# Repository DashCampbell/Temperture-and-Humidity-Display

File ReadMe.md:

# Temperature & Humidity Display

A basic PCB displaying the temperature and humidity from a sensor to a OLED screen.

* Uses a STM32 microcontroller with SWD.
* Uses FreeRTOS to run tasks concurrently.
* Uses I2C to communicate with the OLED display and sensor.
* Uses PWM to controll a RGB addressable LED.

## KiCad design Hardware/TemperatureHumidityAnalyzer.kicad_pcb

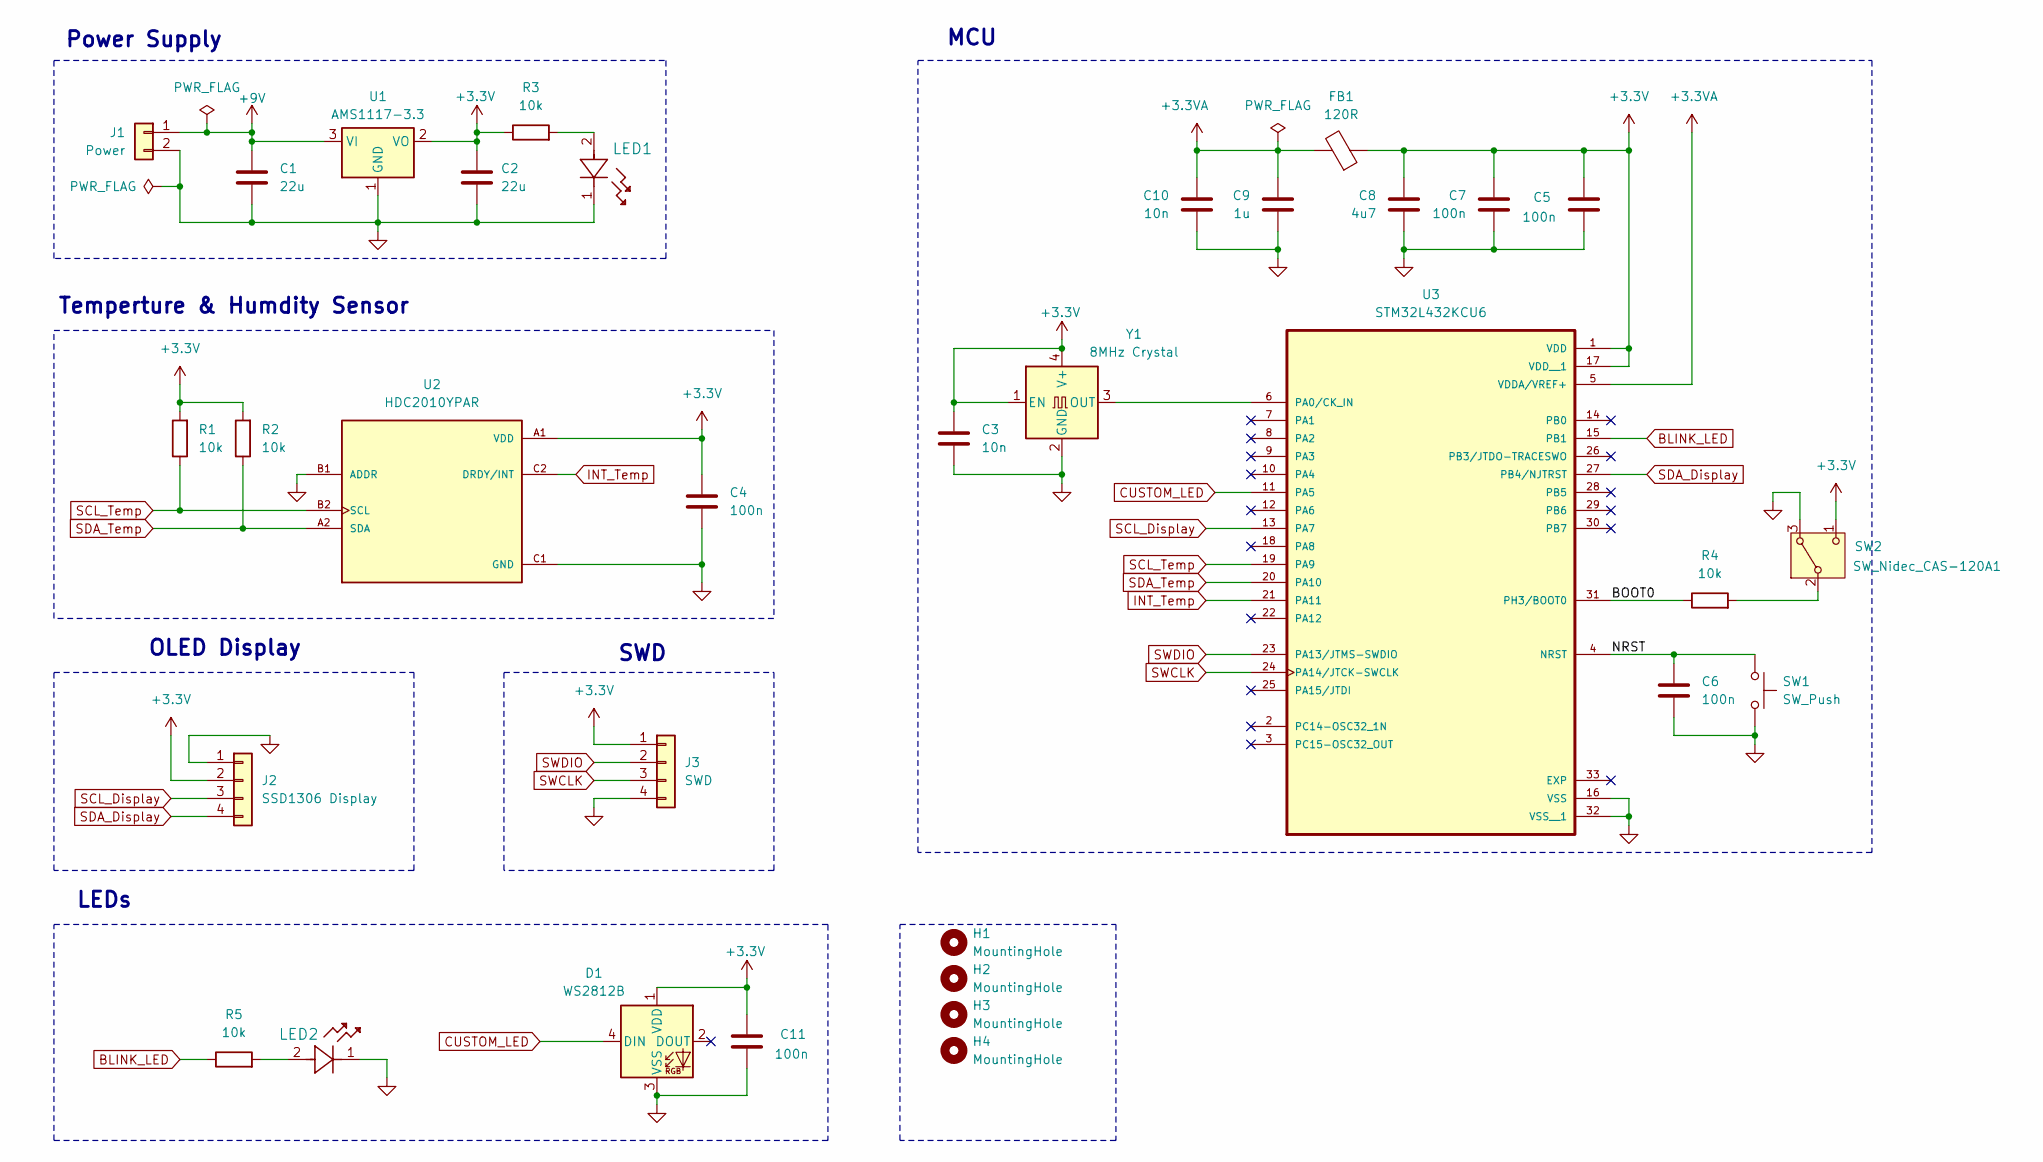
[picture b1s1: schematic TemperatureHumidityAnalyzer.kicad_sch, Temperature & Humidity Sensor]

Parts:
C1, C2: 22u; C_0805_2012Metric_Pad1.18x1.45mm_HandSolder
C3, C10: 10n; C_0603_1608Metric_Pad1.08x0.95mm_HandSolder
C4, C5, C6, C7, C11: 100n; C_0603_1608Metric_Pad1.08x0.95mm_HandSolder
C8: 4u7; C_0603_1608Metric_Pad1.08x0.95mm_HandSolder
C9: 1u; C_0603_1608Metric_Pad1.08x0.95mm_HandSolder
D1: WS2812B; LED_OPSCO_SK6812_PLCC4_5.0x5.0mm_P3.1mm
FB1: 120R; L_0603_1608Metric_Pad1.05x0.95mm_HandSolder
H1, H2, H3, H4: MountingHole; MountingHole_2.2mm_M2
J1: Power; PinSocket_1x02_P2.54mm_Vertical
J2: SSD1306 Display; SSD1306
J3: SWD; PinHeader_1x04_P2.54mm_Vertical
LED1, LED2: LTST-C170KGKT; LED_LTST-C170KGKT_LTO
R1, R2, R4, R5: 10k; R_0603_1608Metric_Pad0.98x0.95mm_HandSolder
R3: 10k; R_0805_2012Metric_Pad1.20x1.40mm_HandSolder
SW1: SW_Push; SW_PUSH_6mm
SW2: SW_Nidec_CAS-120A1; Nidec_Copal_CAS-120A
U1: AMS1117-3.3; SOT-223-3_TabPin2
U2: HDC2010YPAR; BGA6C100X50P2X3_HDC2010YPAR; PARTREV C
U3: STM32L432KCU6; PARTREV 3
Y1: 8MHz Crystal; Oscillator_SMD_EuroQuartz_XO32-4Pin_3.2x2.5mm

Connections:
+3.3V: C2.1, C3.1, C4.1, C5.1, C7.1, C8.1, C11.1, D1.1 (VDD), FB1.1, J2.2, J3.1, R1.2, R2.2, R3.1, SW2.1 (C), U1.2 (VO), U2.A1 (VDD), U3.1 (VDD), U3.17 (VDD__1), Y1.1 (EN), Y1.4 (V+)
+3.3VA: C9.1, C10.1, FB1.2, U3.5 (VDDA/VREF+)
+9V: C1.1, J1.1, U1.3 (VI)
/BOOT0: R4.1, U3.31 (PH3/BOOT0)
/NRST: C6.1, SW1.1, U3.4 (NRST)
BLINK_LED: R5.1, U3.15 (PB1)
CUSTOM_LED: D1.4 (DIN), U3.11 (PA5)
GND: C1.2, C2.2, C3.2, C4.2, C5.2, C6.2, C7.2, C8.2, C9.2, C10.2, C11.2, D1.3 (VSS), J1.2, J2.1, J3.4, LED1.1, LED2.1, SW1.2, SW2.3 (A), U1.1 (GND), U2.B1 (ADDR), U2.C1 (GND), U3.16 (VSS), U3.32 (VSS__1), Y1.2 (GND)
INT_Temp: U2.C2 (DRDY/INT), U3.21 (PA11)
unnamed: LED1.2, R3.2
unnamed: LED2.2, R5.2
unnamed: R4.2, SW2.2 (B)
unnamed: U3.6 (PA0/CK_IN), Y1.3 (OUT)
SCL_Display: J2.3, U3.13 (PA7)
SCL_Temp: R1.1, U2.B2 (SCL), U3.19 (PA9)
SDA_Display: J2.4, U3.27 (PB4/NJTRST)
SDA_Temp: R2.1, U2.A2 (SDA), U3.20 (PA10)
SWCLK: J3.3, U3.24 (PA14/JTCK-SWCLK)
SWDIO: J3.2, U3.23 (PA13/JTMS-SWDIO)

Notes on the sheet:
OLED Display
Power Supply
SWD
Temperture & Humdity Sensor
LEDs
MCU

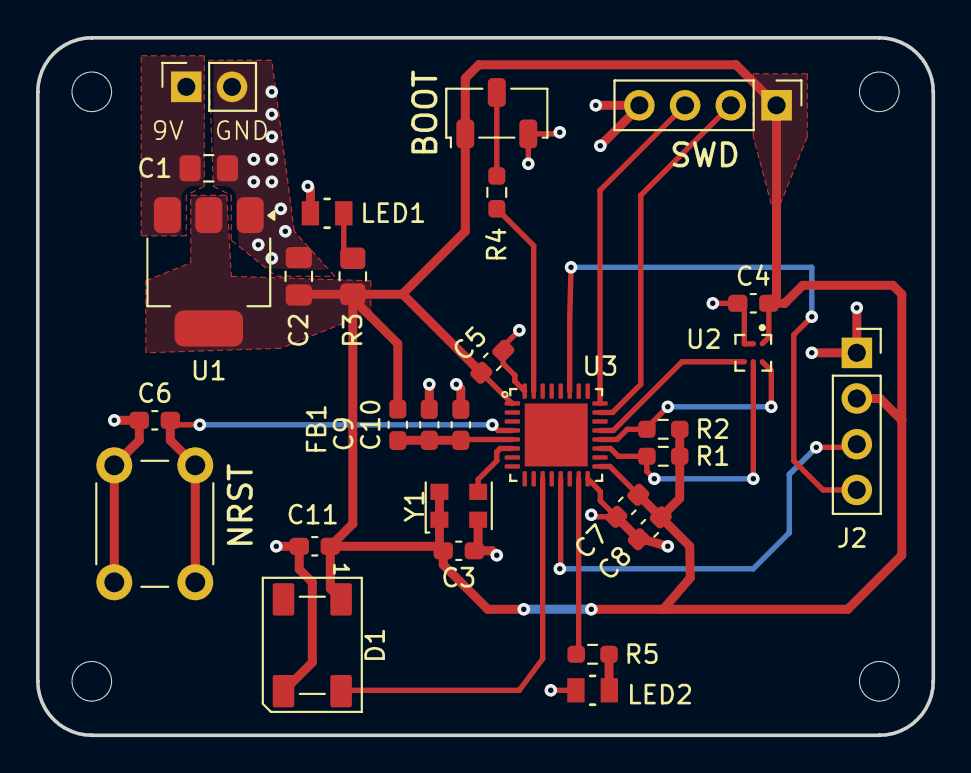
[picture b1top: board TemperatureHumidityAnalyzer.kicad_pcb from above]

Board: 2 copper layers, 49.8 x 38.8 mm, 33 parts (0 on the bottom side), 19 nets.

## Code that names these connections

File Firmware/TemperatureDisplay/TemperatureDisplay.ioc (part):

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Mcu.Name=STM32L432K(B-C)Ux
Mcu.Package=UFQFPN32
Mcu.UserName=STM32L432KCUx
PA0.Mode=HSE-External-Clock-Source-for-LittleOrca
PA0.Signal=RCC_CK_IN
PA10.GPIOParameters=GPIO_Label
PA10.GPIO_Label=SDA_TEMP
PA10.Mode=I2C
PA10.Signal=I2C1_SDA
PA11.GPIOParameters=GPIO_PuPd,GPIO_Label,GPIO_ModeDefaultEXTI
PA11.GPIO_Label=INT_TEMP
PA11.GPIO_ModeDefaultEXTI=GPIO_MODE_IT_FALLING
PA11.GPIO_PuPd=GPIO_PULLUP
PA11.Signal=GPXTI11
PA13\ (JTMS-SWDIO).Mode=Serial_Wire
PA13\ (JTMS-SWDIO).Signal=SYS_JTMS-SWDIO
PA14\ (JTCK-SWCLK).Mode=Serial_Wire
PA14\ (JTCK-SWCLK).Signal=SYS_JTCK-SWCLK
PA5.GPIOParameters=GPIO_Label
PA5.GPIO_Label=PWM_LED
PA5.Signal=S_TIM2_CH1
PA7.GPIOParameters=GPIO_Label,GPIO_Pu
PA7.GPIO_Label=SCL_DISPLAY
PA7.GPIO_Pu=GPIO_PULLUP
PA7.Mode=I2C
PA7.Signal=I2C3_SCL
PA9.GPIOParameters=GPIO_Label
PA9.GPIO_Label=SCL_TEMP
PA9.Mode=I2C
PA9.Signal=I2C1_SCL
PB1.GPIOParameters=GPIO_Label
PB1.GPIO_Label=BLINK_LED
PB1.Signal=GPIO_Output
PB4\ (NJTRST).GPIOParameters=GPIO_Label,GPIO_Pu
PB4\ (NJTRST).GPIO_Label=SDA_DISPLAY
PB4\ (NJTRST).GPIO_Pu=GPIO_PULLUP
PB4\ (NJTRST).Mode=I2C
PB4\ (NJTRST).Signal=I2C3_SDA
RCC.HSE_VALUE=8000000
RCC.SYSCLKFreq_VALUE=80000000
RCC.SYSCLKSource=RCC_SYSCLKSOURCE_PLLCLK
board=custom
